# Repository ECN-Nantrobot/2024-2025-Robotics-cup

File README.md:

# 🤖 2025 Eurobot France Robot from EC NATES Team

This repository contains the software used for our **Eurobot France 2025** mobile robot.

Competition objective (software side):
- move safely on the table,
- pick up cans,
- move them to scoring zones,
- and stack them with a wooden plank,
while coordinating high-level autonomy (Raspberry Pi + ROS2) and low-level actuation (ESP32).

---

## ⚡ Quick Summary (TL;DR)

- This repository is the full competition software stack for our **Eurobot France 2025** robot, split between high-level **ROS2** autonomy on the **Raspberry Pi** and real-time actuator control on the **ESP32**.
- The robot mission flow is: navigate the table, pick cans, transport them, and stack them according to ordered match goals defined in YAML strategies (blue/yellow team variants).
- On the ROS2 side, `main_node` coordinates mission sequencing, ESP synchronization, and runtime state progression, while `laser_to_pointcloud_node` converts LiDAR scans into map-frame pointcloud data.
- Perception updates an OpenCV-backed maze/occupancy representation; close LiDAR points are used for collision-aware behavior and safety reactions during execution.
- The planning stack includes A* path search and Elastic Band smoothing/optimization modules to turn discrete routes into smoother, obstacle-aware motion references.
- Raspberry Pi and ESP32 communicate over serial (`/dev/esp32`) with command/ack/state messages so high-level decisions and low-level actions stay synchronized.
- Deployment supports both manual ROS launching and automatic startup with `one_go.service`; additional operator setup/troubleshooting notes are collected in `noted.md`.
- The detailed sections below explain architecture layers, data flow, planning internals, state-machine behavior, build/run steps, and autostart operations.

---

## 🎥 Competition links

- **YouTube live stream (competition):** https://www.youtube.com/watch?v=Y8KNj2Q6Nss
- **Official Eurobot 2025 page:** https://www.eurobot.org/eurobot-contest/eurobot-2025/

---

## Photos

<p align="center">
   
  <br>
  
</p>

---

## 1) System architecture (code architecture, not just file tree)

The software is designed as a **layered robotics stack**.

## 🎯 Layer A — Match strategy and mission sequencing (ROS2)
Responsibility 📌:
- load team strategy (blue/yellow),
- keep an ordered goal list,
- advance mission state machine,
- synchronize with ESP (start/reset/ack/state).

Core behavior ⚡:
- `main_node` loads YAML goals and robot tuning parameters.
- It sends high-level goals and PID/speed values over serial.
- It tracks progress and decides when to move to the next objective.

---

## Layer B — Environment modeling and local world update (ROS2 + OpenCV + PointCloud)
Responsibility 📌:
- convert raw LiDAR scans into useful obstacle information,
- maintain occupancy/maze image representation,
- mark dangerous/blocked regions around detected clusters.

Core behavior ⚡:
1. LiDAR `/scan` is projected to PointCloud2 and transformed into map frame.
2. Point cloud is filtered and clustered.
3. Cluster centers are smoothed over time.
4. Circular obstacle areas are written into the map image (OpenCV-backed maze).

This is what gives the planner a live, robot-centric table understanding.

---

## Layer C — Path planning and path shaping (A* + Elastic Bands)
Responsibility 📌:
- compute traversable path from robot to current goal,
- refine the path for smooth and obstacle-aware motion.

### A* planner (global/discrete path)
- The codebase includes a generic templated **A\*** implementation.
- It builds a search tree with open/closed sets and returns an ordered path.
- Utility functions exist to save/load A* paths for debugging.

### Elastic Bands optimizer (path smoothing/optimization)
- The codebase also contains an **Elastic Band** optimizer:
  - path resampling (`resizePath`),
  - spring force term (path smoothness),
  - repulsive force term (obstacle clearance),
  - corridor checks and obstacle repulsion,
  - Gaussian smoothing for final trajectory quality.
- It queries obstacle distance using the maze distance transform for fast collision pressure.

> Important: in the current `main.cpp`, parts of A* and Elastic Band usage are present but some calls are commented while mission logic still runs via goal sequencing and safety/obstacle updates.

---

## Layer D — Motion command bridging (ROS2 ↔ ESP32 serial protocol)
Responsibility 📌:
- convert ROS-level goals/tuning into compact serial commands,
- receive acknowledgements and finite state updates from ESP.

Core behavior ⚡:
- ROS sends messages such as:
  - `GOALS:...`
  - speed/PID command payloads,
- ROS parses incoming messages such as:
  - `ACK:...`
  - `RESET`
  - state updates.

This bridge is the contract between navigation intelligence and hardware execution.

Communication behavior in practice:
- The Raspberry Pi opens the ESP link on `/dev/esp32` and waits for startup synchronization.
- During startup, ROS waits for trigger/state messages (including start/team-color flow) before mission execution.
- ROS then sends:
  - speed and PID tuning,
  - the ordered mission goals,
  - additional control messages tied to match progress.
- ESP acknowledges received commands and reports current execution state back.
- If ROS receives a reset/state change, the mission controller in `main_node` can re-initialize and safely re-sync.

---

## Layer E — Real-time low-level control (ESP32 firmware)
Responsibility 📌:
- deterministic wheel/servo/pump/stacking control,
- panel/safety handling,
- sensor and actuator timing not suitable for Linux user-space jitter.

Core behavior ⚡:
- Execute movement primitives and mechanism sequences.
- Handle pickup/stacking actions.
- Return status to ROS so high-level state machine can continue.

---

## Layer F — Launch/runtime orchestration
Responsibility 📌:
- bring up the complete runtime graph reliably.

Core behavior ⚡:
- ROS launch starts TF/static transform, robot state publisher, LiDAR driver, pointcloud transform, and main autonomy node.
- systemd service can autostart all of this on Raspberry Pi boot.

---

## 🔄 2) Data flow between components

End-to-end loop:
1. **LiDAR driver** publishes `/scan`.
2. **`laser_to_pointcloud_node`** transforms to `/pointcloud` in map frame.
3. **`main_node`** updates the OpenCV maze from clustered points.
4. **LiDAR-based collision detection** marks too-close obstacle points and can trigger emergency/safety behavior in the control loop.
5. Planner/mission logic chooses next movement objective.
6. ROS sends goal/tuning messages to ESP32 via serial (`/dev/esp32`).
7. ESP32 executes motors/servos/pump/stacking and reports state.
8. ROS advances mission state and repeats until final objective.

---

## 🧠 3) ROS2 package functionality details (`robonav`)

### 3.1 Main autonomy node
`main_node` integrates:
- serial handshake with ESP,
- team color + start synchronization,
- loading strategy YAML (`goals_blue_final.yaml` / `goals_yellow_final.yaml`),
- publication of odom/path/goals visualization topics,
- pointcloud-based obstacle map updates,
- LiDAR-based close-obstacle filtering for emergency/collision-aware behavior,
- mission progression logic.

State-machine perspective of the main loop:
- **Init / sync state**: open serial, wait for ESP availability, wait for START + team-color context.
- **Configuration state**: load YAML strategy, apply speed/PID, send goals and config payloads to ESP.
- **Run state**: execute mission step-by-step while continuously processing LiDAR-derived obstacle updates.
- **Transition state**: when a goal/action is completed and acknowledged, advance to next strategic step.
- **Safety/reset state**: if reset/emergency conditions are detected, stop or reinitialize and return to a safe synchronization phase.

This state-machine behavior is what coordinates high-level ROS mission logic with low-level ESP execution confirmations.

### 3.2 LiDAR transform node
`laser_to_pointcloud_node`:
- subscribes to `/scan`,
- projects scan to PointCloud2,
- transforms cloud into map frame via TF2,
- publishes `/pointcloud` for planning/perception pipeline.

### 3.3 Map model with OpenCV (`Maze`)
The Maze abstraction provides:
- occupancy image manipulation,
- obstacle rendering (with borders/safety margins),
- precomputed distance transform,
- fast `getDistanceToObstacle()` lookup used by path optimization forces.

This OpenCV map is central to both collision logic and path quality.

### 3.4 A* planning module
The A* module supports:
- reusable generic node-based search,
- heuristic + g/f cost handling,
- parent tree reconstruction of final path,
- optional path persistence to files for debugging and replay.

### 3.5 Elastic Bands module
The Elastic Band module supports:
- iterative path optimization,
- spring/repulsive forces,
- adaptive spacing and corridor correction,
- smoothing using Gaussian kernel,
- optional visualization utilities.

Use case:
- A* gives a valid path,
- Elastic Band transforms it into smoother, safer motion references.

### 3.6 Strategy and configuration
Competition behavior is configured through YAML:
- wheel geometry,
- speed/PID defaults,
- ordered goals for each team color,
- obstacle templates.

---

## ⚙️ 4) ESP32 firmware functionality (control architecture)

The ESP firmware acts as a **real-time execution controller**.

Major functional blocks:
- drivetrain motion control,
- servo control,
- pump control,
- stacking sequence management,
- power monitoring,
- control panel / emergency and safety handling,
- command parser for ROS serial protocol.

Design intent:
- ROS does “what to do next”,
- ESP does “how to move and actuate now”.

---

## 🛠️ 5) Technologies used

### Raspberry Pi / ROS side
- ROS 2 Humble
- C++17
- Python ROS launch
- OpenCV (map and image operations)
- PCL + laser_geometry + TF2 (pointcloud and transforms)
- yaml-cpp (strategy/config loading)
- systemd (autostart)

### ESP side
- PlatformIO
- Arduino framework (ESP32)
- AccelStepper, ContinuousStepper, TFT_eSPI, INA219, PWM servo driver

---

## ⏱️ 6) Runtime sequence during a match

1. Boot RPi and ESP.
2. Launch ROS graph (manual or systemd).
3. Wait for ESP start/team-color synchronization.
4. Load corresponding team goals.
5. Start mission loop:
   - perceive obstacles,
   - update map,
   - plan/shape motion,
   - send commands,
   - execute pickup/stacking actions,
   - verify state and continue.
6. End at final strategic goal.

---

## 🚀 7) Build and run

### 🧪 ROS2 workspace (RPi)
```bash
colcon build --symlink-install
source install/setup.bash
ros2 launch robonav launch.launch.py
```

### 🔋 ESP firmware
- Open `Firmware/` with PlatformIO.
- Build and upload to ESP32.
- Ensure serial mapping is correct (`/dev/esp32` expected on RPi side).

---

## 🔁 8) Autostart (RPi)
Use the provided service assets to launch on boot:
- `src/robonav/autostart/one_go.sh`
- `src/robonav/autostart/one_go.service`

Then monitor:
```bash
journalctl -u one_go.service -f
```

---

## 📝 9) Practical operations notes

- Always confirm team color strategy file before match.
- Validate LiDAR and ESP serial devices after reboot.
- Keep ROS and firmware commits synchronized.
- Perform full mechanism test (pickup/stacking) before table deployment.

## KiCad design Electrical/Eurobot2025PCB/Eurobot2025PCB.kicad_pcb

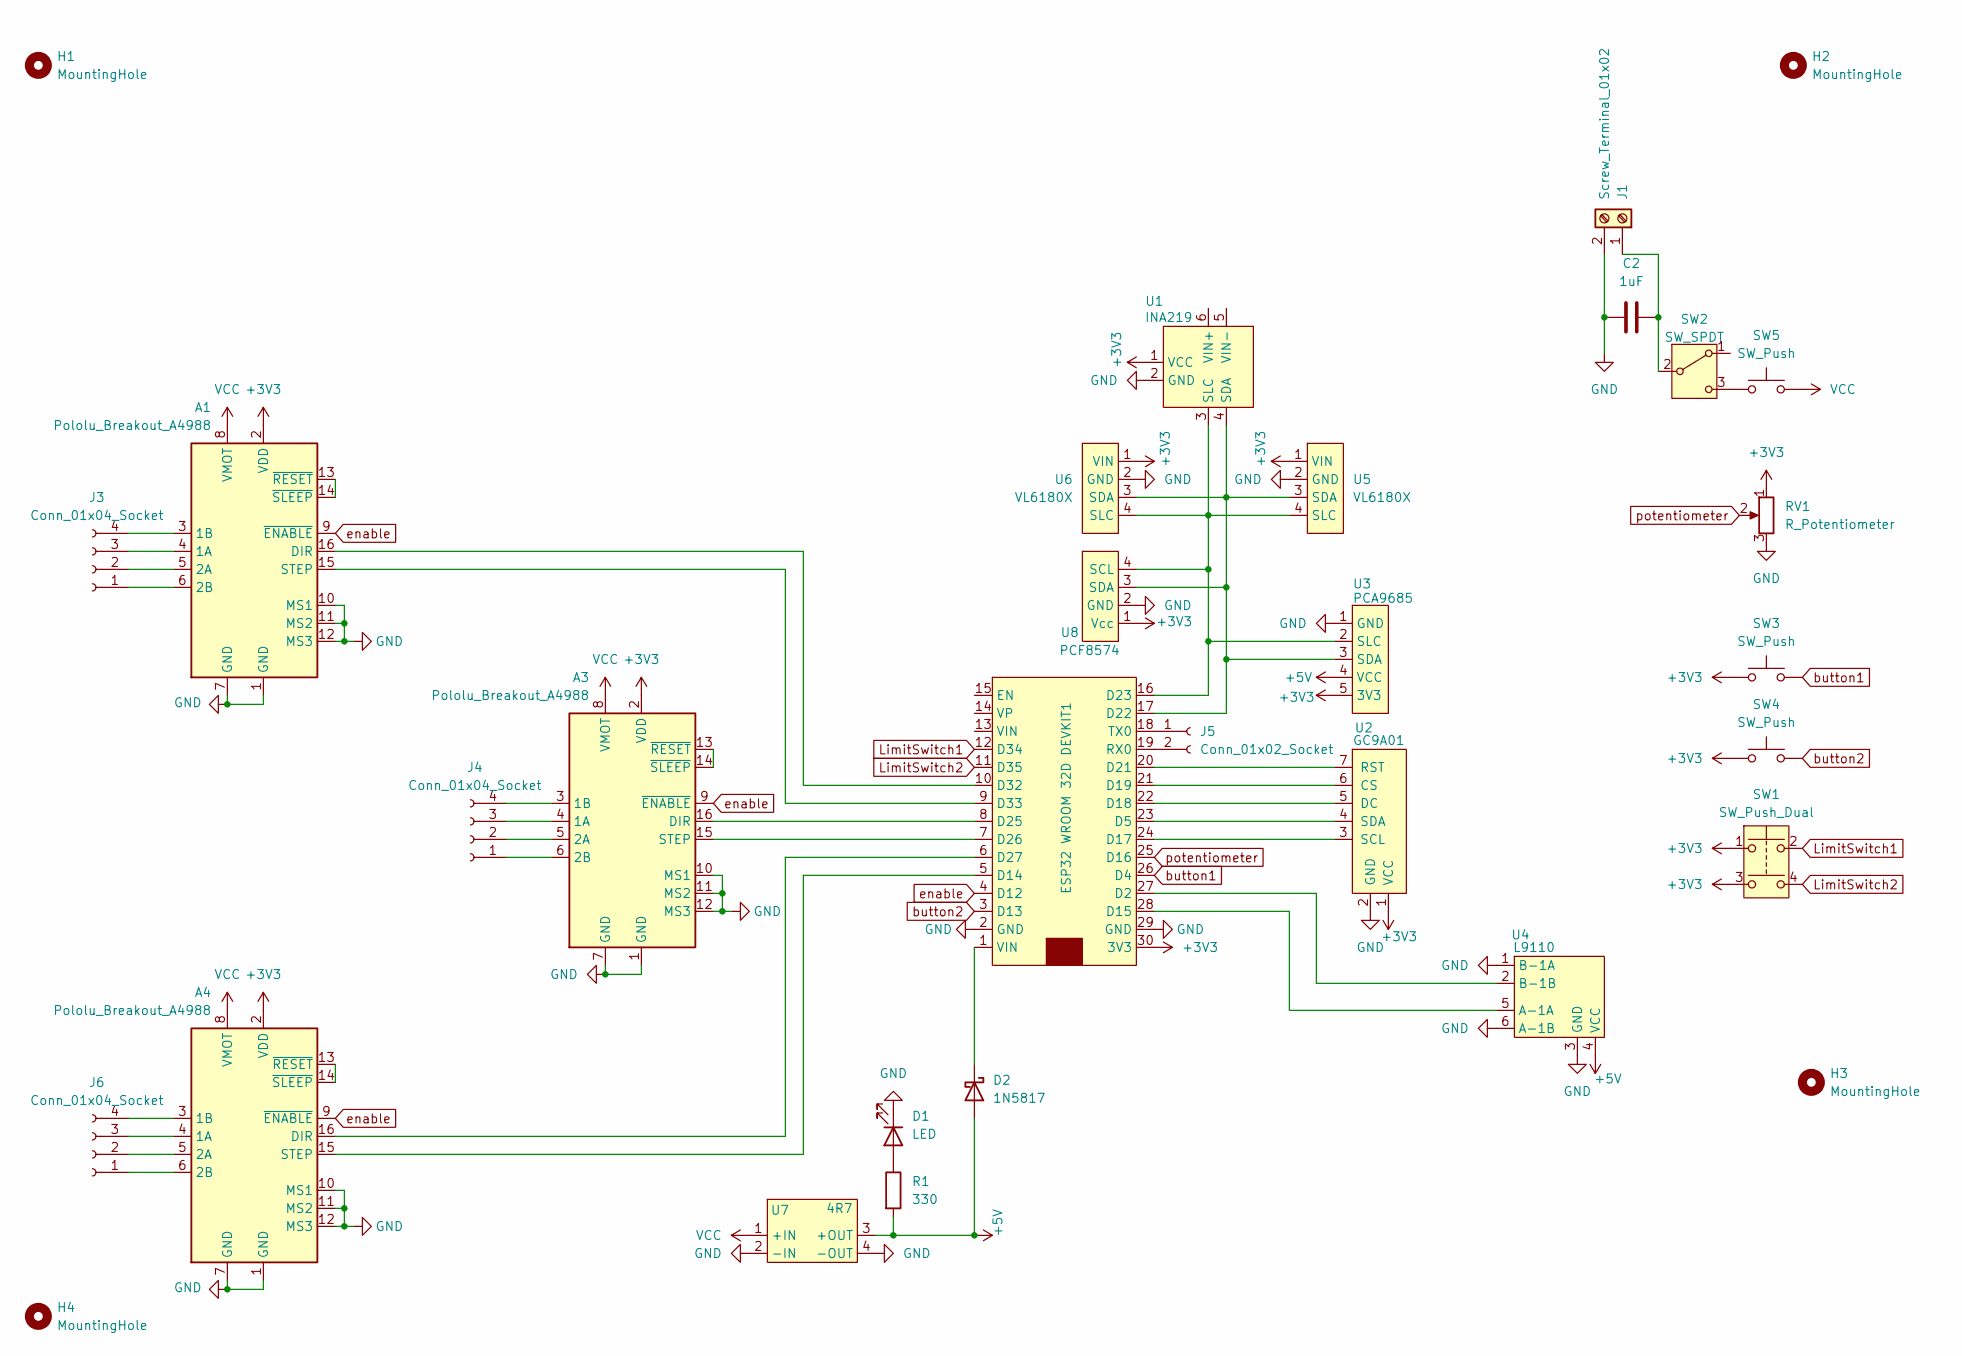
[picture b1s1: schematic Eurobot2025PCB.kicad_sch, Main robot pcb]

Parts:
A1, A3, A4: Pololu_Breakout_A4988; A4988
C2: 1uF; C_Radial_D5.0mm_H11.0mm_P2.00mm
D1: LED; LED_D5.0mm
D2: 1N5817; D_DO-41_SOD81_P10.16mm_Horizontal
ESP32 WROOM 32D DEVKIT1: ESP32 WROOM 32D
H1, H2, H3, H4: MountingHole; MountingHole_3.2mm_M3
J1: Screw_Terminal_01x02; TerminalBlock_MetzConnect_Type059_RT06302HBWC_1x02_P3.50mm_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
J3, J4, J6: Conn_01x04_Socket; JST_XH_B4B-XH-A_1x04_P2.50mm_Vertical
J5: Conn_01x02_Socket; PinHeader_1x02_P2.54mm_Vertical
R1: 330; R_Axial_DIN0207_L6.3mm_D2.5mm_P10.16mm_Horizontal
RV1: R_Potentiometer; PinHeader_1x03_P2.54mm_Vertical
SW1: SW_Push_Dual; PinHeader_2x02_P2.54mm_Vertical
SW2: SW_SPDT; SW_XKB_DM1-16UP-1
SW3, SW4: SW_Push; SW_PUSH_6mm
SW5: SW_Push; JST_XH_B2B-XH-A_1x02_P2.50mm_Vertical
U1: INA219; INA219 DC current sensor
U2: GC9A01; PinHeader_1x07_P2.54mm_Vertical
U3: PCA9685; PinHeader_1x05_P2.54mm_Vertical
U4: L9110
U5, U6: VL6180X; PinHeader_1x04_P2.54mm_Vertical
U7: 4R7
U8: PCF8574; PinHeader_1x04_P2.54mm_Vertical

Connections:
+3V3: A1.2 (VDD), A3.2 (VDD), A4.2 (VDD), ESP32 WROOM 32D DEVKIT1.30 (3V3), RV1.1, SW1.1, SW1.3, SW3.1, SW4.1, U1.1 (VCC), U2.1 (VCC), U3.5 (3V3), U5.1 (VIN), U6.1 (VIN), U8.1 (Vcc)
+5V: D2.2 (A), R1.2, U3.4 (VCC), U4.4 (VCC), U7.3 (+OUT)
GND: A1.1 (GND), A1.7 (GND), A1.10 (MS1), A1.11 (MS2), A1.12 (MS3), A3.1 (GND), A3.7 (GND), A3.10 (MS1), A3.11 (MS2), A3.12 (MS3), A4.1 (GND), A4.7 (GND), A4.10 (MS1), A4.11 (MS2), A4.12 (MS3), C2.1, D1.1 (K), ESP32 WROOM 32D DEVKIT1.2 (GND), ESP32 WROOM 32D DEVKIT1.29 (GND), J1.2, RV1.3, U1.2 (GND), U2.2 (GND), U3.1 (GND), U4.1 (B-1A), U4.3 (GND), U4.6 (A-1B), U5.2 (GND), U6.2 (GND), U7.2 (-IN), U7.4 (-OUT), U8.2 (GND)
LimitSwitch1: ESP32 WROOM 32D DEVKIT1.12 (D34), SW1.2
LimitSwitch2: ESP32 WROOM 32D DEVKIT1.11 (D35), SW1.4
unnamed: A1.4 (1A), J3.3
unnamed: A1.3 (1B), J3.4
unnamed: A1.5 (2A), J3.2
unnamed: A1.6 (2B), J3.1
unnamed: A1.16 (DIR), ESP32 WROOM 32D DEVKIT1.10 (D32)
unnamed: A1.15 (STEP), ESP32 WROOM 32D DEVKIT1.9 (D33)
unnamed: A1.13 (~RESET), A1.14 (~SLEEP)
unnamed: A3.4 (1A), J4.3
unnamed: A3.3 (1B), J4.4
unnamed: A3.5 (2A), J4.2
unnamed: A3.6 (2B), J4.1
unnamed: A3.16 (DIR), ESP32 WROOM 32D DEVKIT1.8 (D25)
unnamed: A3.15 (STEP), ESP32 WROOM 32D DEVKIT1.7 (D26)
unnamed: A3.13 (~RESET), A3.14 (~SLEEP)
unnamed: A4.4 (1A), J6.3
unnamed: A4.3 (1B), J6.4
unnamed: A4.5 (2A), J6.2
unnamed: A4.6 (2B), J6.1
unnamed: A4.16 (DIR), ESP32 WROOM 32D DEVKIT1.6 (D27)
unnamed: A4.15 (STEP), ESP32 WROOM 32D DEVKIT1.5 (D14)
unnamed: A4.13 (~RESET), A4.14 (~SLEEP)
unnamed: D1.2 (A), R1.1
unnamed: D2.1 (K), ESP32 WROOM 32D DEVKIT1.1 (VIN)
unnamed: ESP32 WROOM 32D DEVKIT1.27 (D2), U4.2 (B-1B)
unnamed: ESP32 WROOM 32D DEVKIT1.23 (D5), U2.4 (SDA)
unnamed: ESP32 WROOM 32D DEVKIT1.28 (D15), U4.5 (A-1A)
unnamed: ESP32 WROOM 32D DEVKIT1.24 (D17), U2.3 (SCL)
unnamed: ESP32 WROOM 32D DEVKIT1.22 (D18), U2.5 (DC)
unnamed: ESP32 WROOM 32D DEVKIT1.21 (D19), U2.6 (CS)
unnamed: ESP32 WROOM 32D DEVKIT1.20 (D21), U2.7 (RST)
unnamed: ESP32 WROOM 32D DEVKIT1.17 (D22), U1.4 (SDA), U3.3 (SDA), U5.3 (SDA), U6.3 (SDA), U8.3 (SDA)
unnamed: ESP32 WROOM 32D DEVKIT1.16 (D23), U1.3 (SLC), U3.2 (SLC), U5.4 (SLC), U6.4 (SLC), U8.4 (SCL)
unnamed: ESP32 WROOM 32D DEVKIT1.19 (RX0), J5.2
unnamed: ESP32 WROOM 32D DEVKIT1.18 (TX0), J5.1
unnamed: C2.2, J1.1, SW2.2 (B)
unnamed: SW2.3 (C), SW5.1
VCC: A1.8 (VMOT), A3.8 (VMOT), A4.8 (VMOT), SW5.2, U7.1 (+IN)
button1: ESP32 WROOM 32D DEVKIT1.26 (D4), SW3.2
button2: ESP32 WROOM 32D DEVKIT1.3 (D13), SW4.2
enable: A1.9 (~ENABLE), A3.9 (~ENABLE), A4.9 (~ENABLE), ESP32 WROOM 32D DEVKIT1.4 (D12)
potentiometer: ESP32 WROOM 32D DEVKIT1.25 (D16), RV1.2

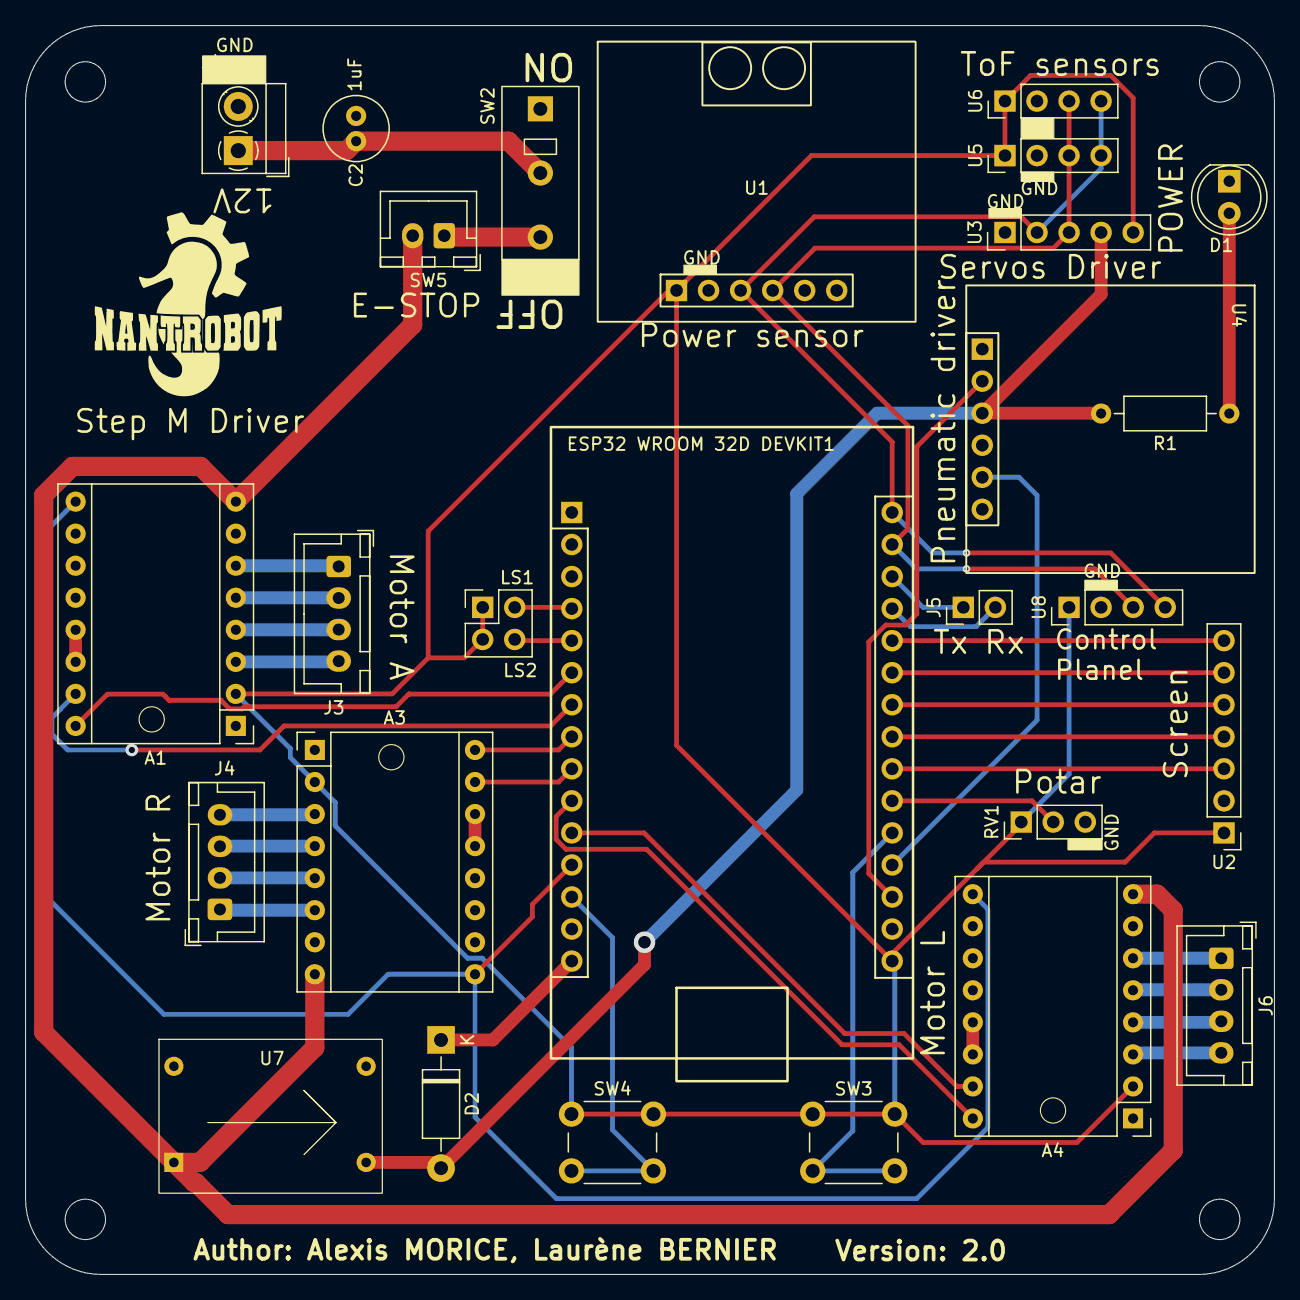
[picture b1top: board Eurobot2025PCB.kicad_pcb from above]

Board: 2 copper layers, 99.0 x 99.0 mm, 31 parts (0 on the bottom side), 46 nets.

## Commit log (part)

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2024-11-06 Add files via upload
    draft of localization code
2024-11-06 Code and schematics for testing the stepper motor
2024-11-06 Tested with defined inputs.
2024-11-07 Adding PlatformIO Project
2024-11-07 Revert
2024-11-20 Add files via upload
    Astar algorithm for path generation
2024-11-27 inital planning commit
2024-11-30 a* algorithm working (wsl), elastic bands not added
2024-12-01 firmware with platform IO for ESP32
2024-12-01 initial elastic bands kind of working and displaying
2024-12-01 EB working, but instable sometimes. Added also visualization of the algorithm
2024-12-02 EB: fixed endpoints, use old a*path if it exist, better displaying
2024-12-04 Update localization.h
    added function to compute motor angle needed to reach the target position
2024-12-04 Update test.cpp
    updated test code to test new function that computes the motor angles required to reach a target position
2024-12-04 Update localization.cpp
    Added the implementation of the function that computes the motor angles required to reach the target position
2024-12-05 EB with float position and commented out debbuging codelines for one circle. Sometimes points stuck becuase displacement to big because of repulsion force. New interactive map generator, not 100% wor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
2024-12-06 made structure and classes... better (I think)
2024-12-07 everything working better, variable radii for eb, reloadable maze for interac, generator, auto formatting, displaying better
2024-12-07 variable spring radius
2024-12-07 save, not finished
2024-12-08 eb working well, obstacle class added, problem with narrow passages, number of pathpoints at beginning and end nnot working very well, and symmetrical abstacles also not
2024-12-08 corridor check and more improvements, point has colour also, speed change and extif functions
2024-12-08 better reppeling on obstacles with random radius, pause with spacebar, final until now
2024-12-09 added better vizualization in savingSolution() and Gaussian smoothing incl. filling gaps
2024-12-10 real map as maze, border around obstacles (darker than 120 gray) at import, 50x faster A*, improved load function in interactive generation
2024-12-11 abstacels and diplaying order better
2024-12-11 updated the firmware with motor test
2024-12-12 a star working with downsized image, elastic band improved, smoothing bug imporved
2024-12-12 working very well, a* downsizes image, elastic band not giggeling, smoothed path good, start is being updated for simulation, FINAL FOR NOW
2024-12-12 control simultiaon for path following
2024-12-13 integrated control simulation and path planning into main loop
2024-12-13 real-time path planning and following in simulation
2024-12-13 fine tuning, passing of a star path only if it differes a lot
2024-12-14 more improvements, astar updadting only when changed enough, better time moitoring
2024-12-15 intermediate commit, added distance transform and slowing down before goal and turnign to obstacle. Slowing down beforre obstacle or goal doesnt work and distance transform for a satr isnt faster and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
2024-12-15 added state maschine and multiple goal
2024-12-16 added proximity moving obstacle sesor, turn to path, vizulisation of sensor and transparent eb ...
2024-12-18 improvements in elcastic band and A* setting and caculating
2024-12-19 update values for wheelDiameter and trackWidth
2024-12-19 remove firmware
2024-12-19 Update localization.cpp
    added followPath function. The 3 functions updatePose, computeWheelAngles and followPath will be added in the arduino code of the Esp32 to control the motor with the number of steps to turn.
2024-12-19 motor test follow path from file Ferdinand
2025-01-11 Test HC-SR04 ultrasonic sensors
2025-01-29 Banner V1
2025-01-29 Added missing motorHandler.h file
2025-01-29 Test ContinuousStepper in stead of AccelStepper and it worked
2025-01-31 follow path should workwith continousstepper
2025-02-05 Test of range sensor VL6180X
2025-02-05 interim version with Hayato and Alessandro of path following
2025-02-05 cleaned up
2025-02-05 Runge Kutta integration
2025-02-05 changes for file save
2025-02-06 CAD for first version of battery holder
2025-02-08 ros2 added for maze, not yet gazebo
2025-02-08 connected to gazebo, almost moving
2025-02-08 rviz and gazebo
2025-02-08 robot is in rviz and gazebo in playmat and can be controlled by keyboard
2025-02-09 should be working but controlmanager is not and /opt/ros/humble/share/gazebo_ros2_control/gazebo_ros2_control_plugins.xml is missing
2025-02-10 Stop tracking install/ directory
2025-02-10 CAD parts for stacking mecanism
2025-02-10 robot moving
2025-02-10 sned /cmd_vel from main
2025-02-11 robot pathfollowing and simple world gazebo, path in rviz
2025-02-12 maps
2025-02-12 Updated Moving Frame.
    PLEASE NOTE: The mounting holes for the limit switch (10t85) need to be verified with below datasheet and real part. (https://www.chinadaier.com/wp-content/uploads/2017/08/Micro-switch.pdf)
2025-02-13 removed dt, dt = real execution time, improved some things, but still different in gazbeo
2025-02-13 using /odom to get the position, and it works in gazebo
2025-02-14 added ros time, tried adding map and image but didnt work, position from dt still doesnt work
2025-02-22 Add kicad pcb project
2025-02-25 CAD for pneumatic actuator
2025-02-26 ajout pièce support pompe (axe x)
2025-02-26 adding pump support
    adding pump support
2025-02-26 add z axis and corrections for x axis
2025-02-26 robotics club meeting
2025-03-01 Add 4th step motor and 12V to 5V converter to PCB
2025-03-05 refactor the main firmware to implement freeRtos and added the pio folder to have the display setup
2025-03-05 not much new, lidar sim not working
2025-03-06 Test of vacuum
2025-03-06 Function to initialize the stepper motor for horizontal movement
2025-03-07 added corresponding Firmare from main
2025-03-07 recieving position 1
2025-03-07 recieving position 2
2025-03-08 serial lib
2025-03-08 Fix: Füge serial als normales Verzeichnis hinzu
2025-03-08 deploy script
2025-03-09 communication working, not moving 1
2025-03-09 communication working, not moving 2
2025-03-09 working better but robot is moving wrong
2025-03-09 working better but robot is moving wrong 2
2025-03-09 brouillon pour l'axe Z qui porte l'axe X
2025-03-09 working but sychronisation not sure
2025-03-09 working but sychronisation not sure 2
2025-03-10 Updated front actuator (=first one printed)
2025-03-10 updated some of the CAD
2025-03-12 updated CAD
2025-03-13 communication working, esp driving wrong 1
2025-03-13 communication working, esp driving wrong 2
2025-03-13 rviz vizualization, but robot model not moving and robot moving weird, path sending is taking long
2025-03-15 checkpoint1
2025-03-15 checkpoint
2025-03-17 Update init function
2025-03-17 script to get the mac address of an esp32 board
2025-03-17 everything working exept for path sending
2025-03-18 Automatic commit for build and deploy
2025-03-18 Reorganised CAD folder
    Moved all standard parts to a separate folder
    Change naming convention : ALL_CAPITAL for standard parts and Snake_case for custom made parts
2025-03-19 working fine exept path sending and PID
2025-03-19 path working, but slow
2025-03-19 added X axis initialisation
2025-03-19 working better but still not
2025-03-19 updated pcb
2025-03-19 update pcb
2025-03-19 ajout base axe Z
2025-03-19 supp temp
2025-03-19 working on real ronbot but bad PID
2025-03-19 added rplidar package
2025-03-20 Navigation with RPI and ESP mostly working good
2025-03-20 added map to rviz but not correct
2025-03-20 Path following and communication with RPI and RSP working! Also vizualization in RVIZ
2025-03-24 Real robot test and Goal code updated but needs more improvement
2025-03-26 CAD robot V1
2025-03-26 Lidar in gazebo working
2025-03-26 FRONT actuator side
2025-03-26 Robot driving and turning correctly to goalsgit status! (Band ath little zigzag but I dont know why
2025-03-26 Lidar specs from C1, added poles in draft.world and ready for lidar programming
2025-03-29 added AMCL and laser to pointcloud2 but not yet tuned
2025-03-29 added playground map to rviz and amcl position usage instead of odom (can be switched to)
2025-03-30 Added Obstacle ecognition inside map area
2025-03-30 amcl tuned better, on bord bacon d=70mm
2025-03-30 tuned, robot beacon 100x100mm, centre of cluster is obstacle
2025-03-30 added big robot, removed base_footprint, smoothing for obstacle...
2025-04-01 removed uneccecary stuff from rpi, fixed slow down before goal, added slow down when starting turning (not quite), display astar path (not quite) and elastic band circles
2025-04-01 yaml file for params, slowing down/speeding up, vizualization in rviz, path sending time printed
2025-04-01 added big robot and tuned pid and settings
2025-04-02 added maps, added pole gazebo world and map
2025-04-03 lidar getting scan and rest almost wokring
2025-04-03 lidar and map and everything running
2025-04-03 lidar working and amcl working but is really bad and only testable with robot and odometry
2025-04-09 meeting, reduced steps count
2025-04-26 update pcb :alien:
2025-05-07 robotics lab try
2025-05-07 robotic lab meeting
2025-05-15 meeting, obstacles on map but wrong, on /map_vis topic, wainting for esp
2025-05-15 add a service and a bash script for auto launch
2025-05-22 Lots of changes in CAD
2025-05-22 Loads of changes
2025-05-22 inbetween, lookup error for pointn cloud transform
2025-05-23 cleanup and all_goals file and not working script to plot them
2025-05-23 plot_goals.py updated but still wrong
2025-05-23 Obstacle Detection working, not yet moving, cleaned up files
2025-05-23 wokring but not moving vorrectly
2025-05-23 lttle updates but esp not resetting
2025-05-24 LiDAR finally working but circles on map not perfect, together with esp kind of
2025-05-24 obstacle detection final, working, added waitforpathstate
2025-05-24 changrd wheel distance to 37,6mm and made robot model good for rviz
2025-05-24 corrected goal positions and goal plotting
2025-05-24 added start from esp (rpi waits), added colour choosing almost, reset almost from esp, changed speed, wheel diameter
2025-05-24 strategy files for team blue and yellow added
2025-05-24 obstacles can be added from yaml file, other lidar approcah is the same as in lidar_link frame
2025-05-24 added restart
2025-05-26 rosbags, tf still not working, but the rest is
2025-05-26 rviz config
2025-05-26 Add PAMI firmware
2025-05-28 working wiht lidar and my code 1.
2025-05-28 before adding libraries to esp
2025-05-28 libaries2
2025-05-28 compiling but esp error control panel
2025-05-28 working with autostart sudo systemctl start one_go.service
2025-05-28 first try, band not good, button ok goals not good, fuck this shiiit
2025-05-28 added emergency stop
2025-05-28 not running but emergency stop and timer added
2025-05-28 working for homologation
2025-05-29 fix setup
2025-05-29 first match
2025-05-29 added the straight path
2025-05-29 sime improvements
2025-05-29 2nd match with straight path but didnt move
2025-05-29 Pami working day 2
2025-05-29 SuperStar firmaware
    TODO: add files for the path
2025-05-29 working wiht straight paths, rviz vis, and pathplannung on esp and correct usb automatic on rpi
2025-05-30 3. match
2025-05-30 with autostart working and push cans one time test
2025-05-30 one push working with simple backwards, sometimes jitter, better packwards not working
2025-05-30 added Code for pushing all wiht also servos but not tested
2025-05-30 4th match one push, wait and go tomccc
2025-05-30 4th match one push WORKINF WELL, with autostart, wait and go to the back
2025-05-30 LED for status of RPI, and Code for multi push with servo test
2025-05-30 NOW CORRECT, smal led mistake
2025-05-31 changes not checked for final match
2026-03-13 Add formatted noted.md with RPi setup, service, and ops notes
2026-03-13 Expand TL;DR summary with richer system context
2026-04-04 Add competition links and emojis to README
2026-04-04 Add more emojis across README sections
2026-04-04 Add competition photo gallery section and image placeholders
2026-04-04 Added images nicely to README
